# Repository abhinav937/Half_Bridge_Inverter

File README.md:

# for commits on or before Mar 10 2023, the main folder should be renamed as RnD_6th_sem when opened with KiCad. <br/>
## Make sure the folder name is same as the kicad project file name.

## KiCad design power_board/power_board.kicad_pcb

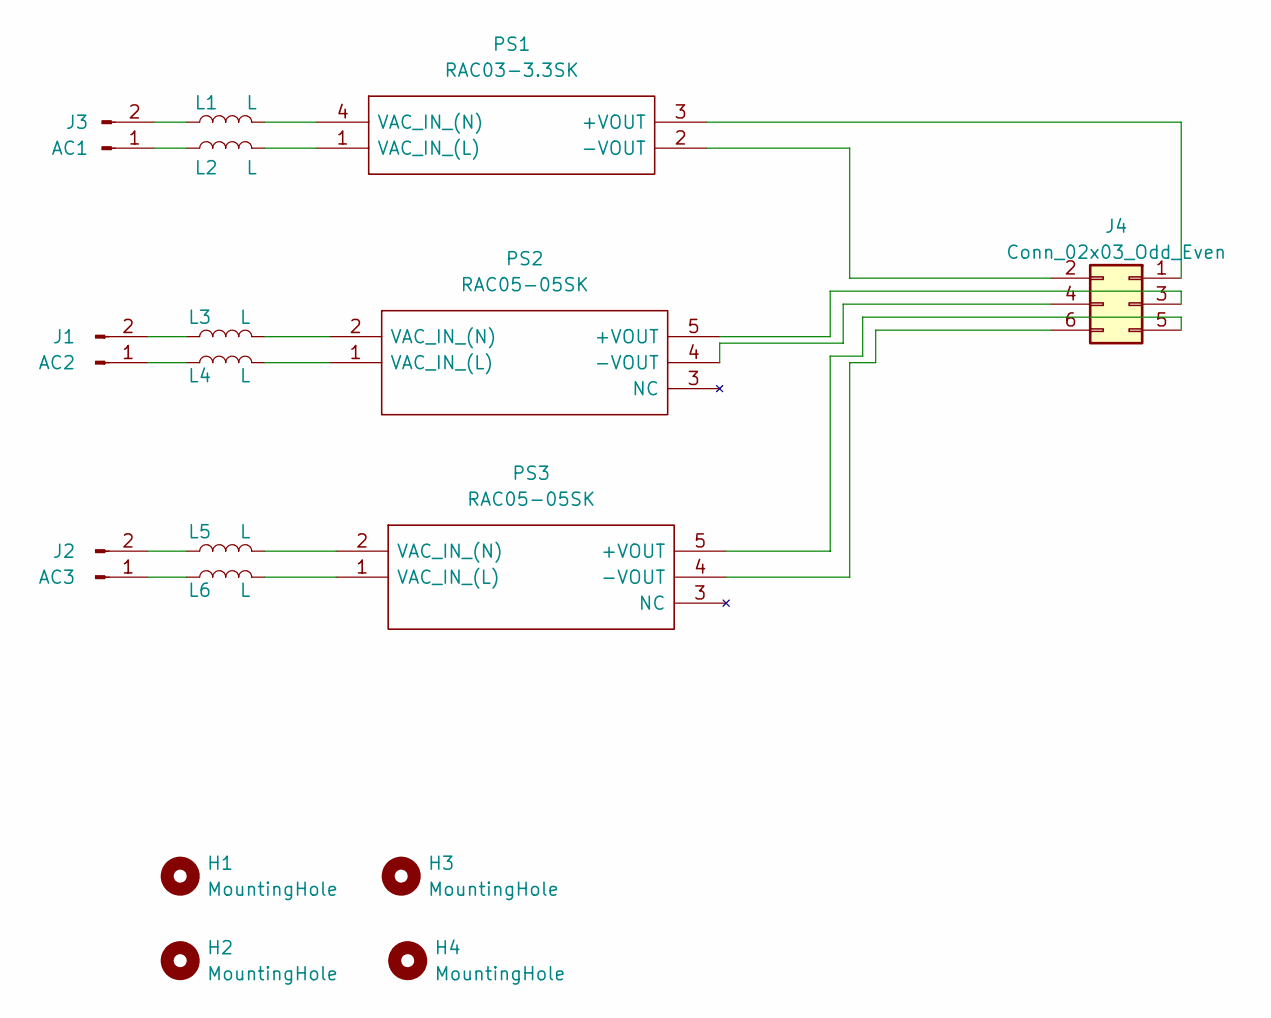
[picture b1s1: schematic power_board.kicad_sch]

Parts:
H1, H2, H3, H4: MountingHole; MountingHole_3.2mm_M3
J1: AC2; Molex_KK-396_A-41791-0002_1x02_P3.96mm_Vertical
J2: AC3; Molex_KK-396_A-41791-0002_1x02_P3.96mm_Vertical
J3: AC1; Molex_KK-396_A-41791-0002_1x02_P3.96mm_Vertical
J4: Conn_02x03_Odd_Even; PinHeader_2x03_P2.54mm_Horizontal
L1, L2, L3, L4, L5, L6: L; C_Rect_L7.0mm_W3.5mm_P5.00mm
PS1: RAC03-3.3SK; RAC0305SK; Mouser Part Number 919-RAC03-3.3SK
PS2, PS3: RAC05-05SK; RAC0505SK; Mouser Part Number 919-RAC05-05SK

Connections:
unnamed: J1.1, L4.1
unnamed: J1.2, L3.1
unnamed: J2.1, L6.1
unnamed: J2.2, L5.1
unnamed: J3.1, L2.1
unnamed: J3.2, L1.1
unnamed: J4.1, PS1.3 (+VOUT)
unnamed: J4.2, PS1.2 (-VOUT)
unnamed: J4.3, PS2.5 (+VOUT)
unnamed: J4.4, PS2.4 (-VOUT)
unnamed: J4.5, PS3.5 (+VOUT)
unnamed: J4.6, PS3.4 (-VOUT)
unnamed: L2.2, PS1.1 (VAC_IN_(L))
unnamed: L1.2, PS1.4 (VAC_IN_(N))
unnamed: L4.2, PS2.1 (VAC_IN_(L))
unnamed: L3.2, PS2.2 (VAC_IN_(N))
unnamed: L6.2, PS3.1 (VAC_IN_(L))
unnamed: L5.2, PS3.2 (VAC_IN_(N))

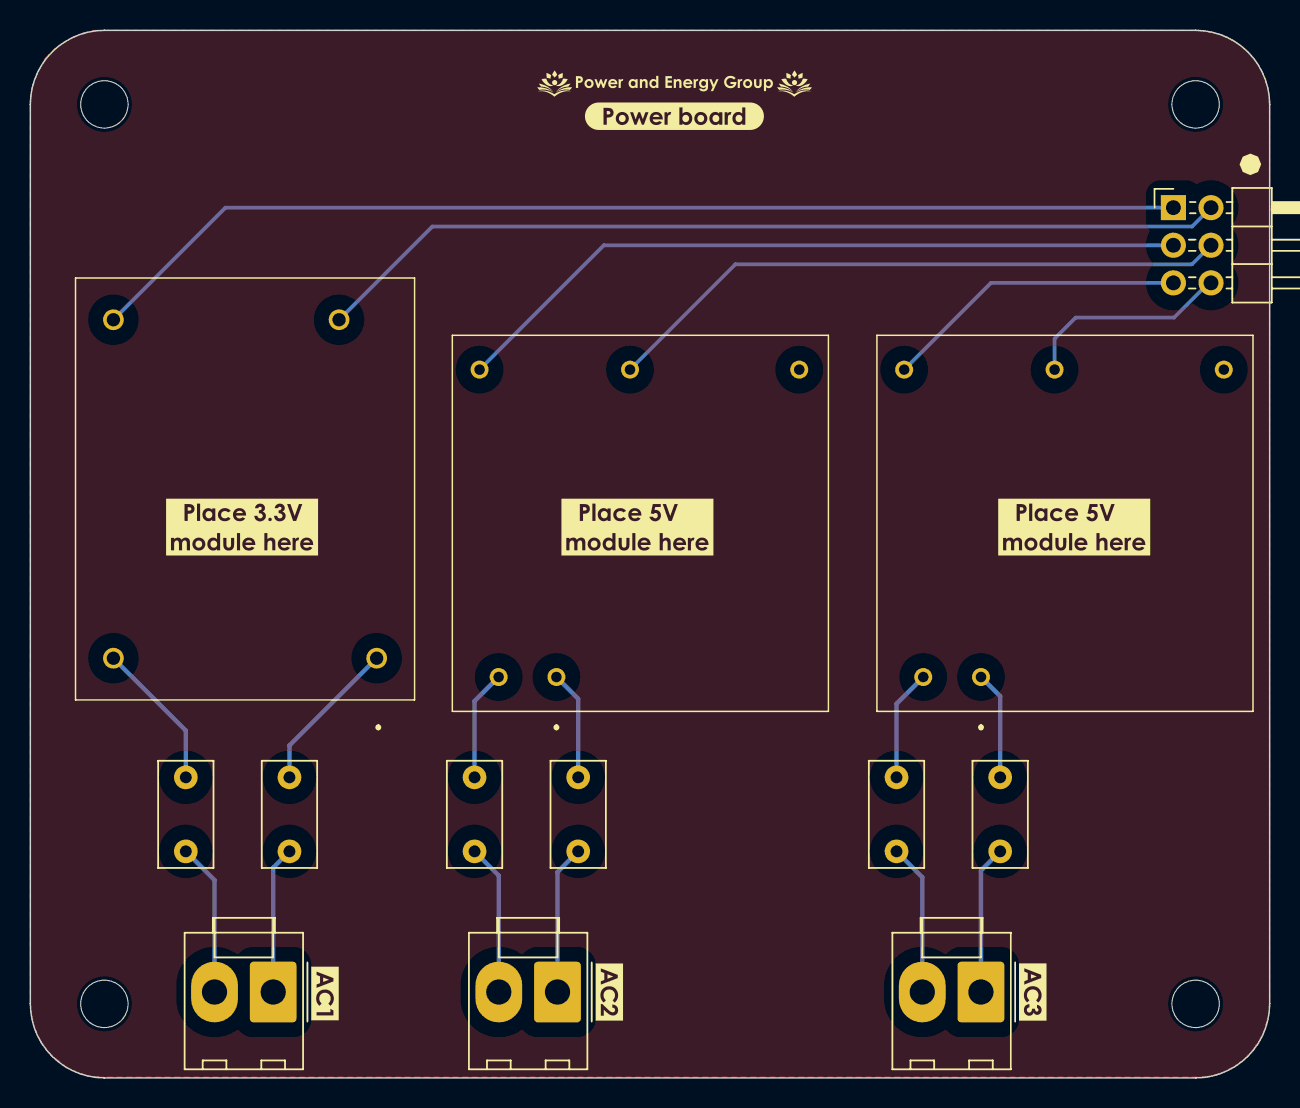
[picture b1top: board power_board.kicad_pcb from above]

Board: 2 copper layers, 83.7 x 70.8 mm, 26 parts (0 on the bottom side), 18 nets.

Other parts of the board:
kibuzzard-63EE9CC7: G***; kibuzzard-63EE9CC7
kibuzzard-63EE9CEB: G***; kibuzzard-63EE9CEB
kibuzzard-63EE9CF3: G***; kibuzzard-63EE9CF3
kibuzzard-63EE9D9B: G***; kibuzzard-63EE9D9B
kibuzzard-63EEA033: G***; kibuzzard-63EEA033
kibuzzard-63EEA069: G***; kibuzzard-63EEA069
kibuzzard-63EEA072: G***; kibuzzard-63EEA072
kibuzzard-640AA3C8: G***; kibuzzard-640AA3C8
kibuzzard-640AA5A5: G***; kibuzzard-640AA5A5

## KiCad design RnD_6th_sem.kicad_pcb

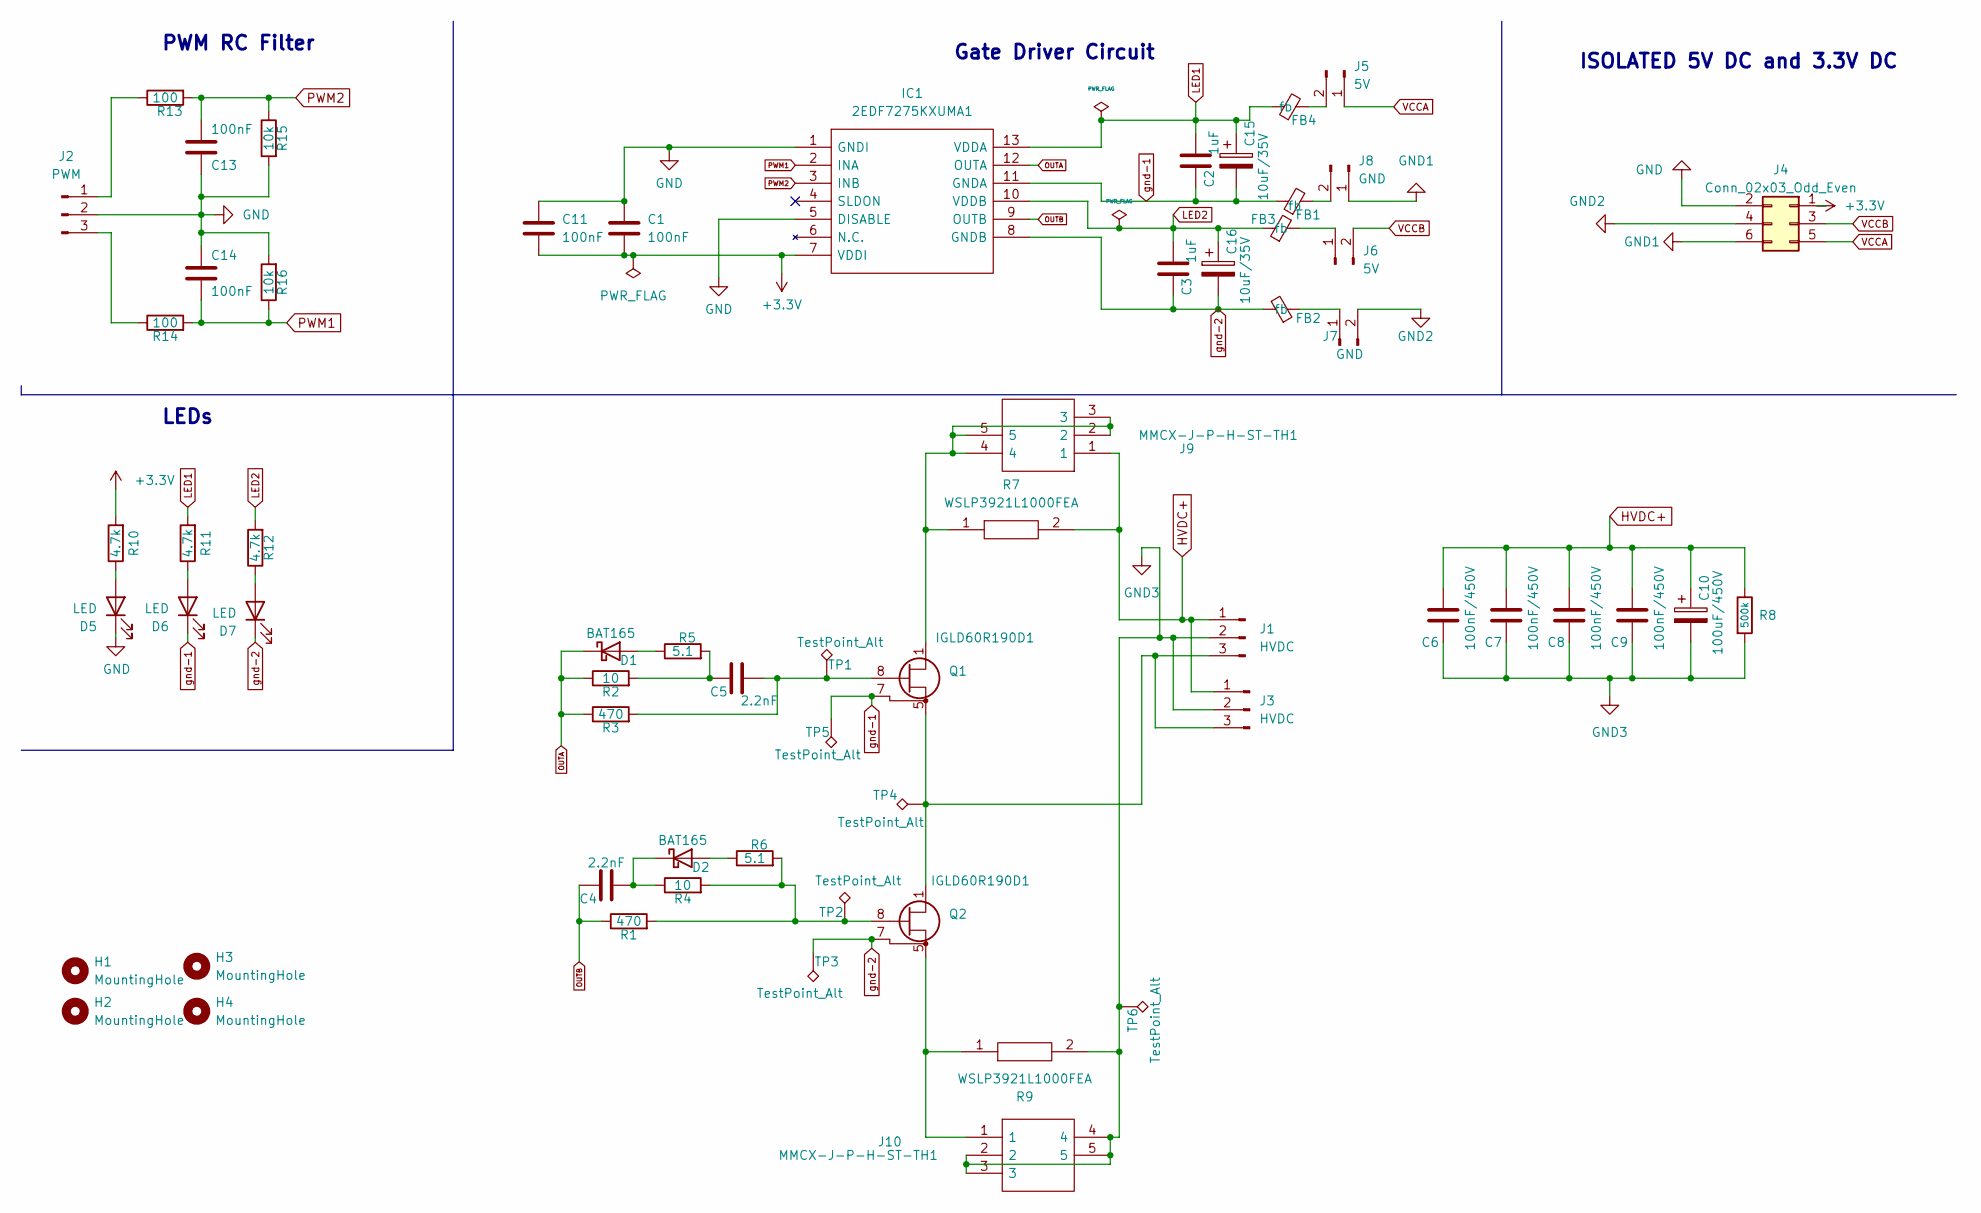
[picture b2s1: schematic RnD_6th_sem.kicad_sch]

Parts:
C1, C11, C13, C14: 100nF; C_0805_2012Metric
C2, C3: 1uF; C_0805_2012Metric
C4, C5: 2.2nF; C_0805_2012Metric
C6, C7, C8, C9: 100nF/450V; C_1206_3216Metric
C10: 100uF/450V; CAPPRD750W80D1825H3200
C15, C16: 10uF/35V; CP_Elec_5x5.3
D1, D2: BAT165; D_SOD-323
D5, D6, D7: LED; LED_0805_2012Metric
FB1, FB2, FB3, FB4: fb; R_0805_2012Metric
H1, H2, H3, H4: MountingHole; MountingHole_3.2mm_M3
IC1: 2EDF7275KXUMA1; TFLGA65P500X500X106-14_13N-V; Mouser Part Number 726-2EDF7275KXUMA1
J1, J3: HVDC; Molex_KK-396_A-41791-0003_1x03_P3.96mm_Vertical
J2: PWM; Molex_KK-254_AE-6410-03A_1x03_P2.54mm_Vertical
J4: Conn_02x03_Odd_Even; PinSocket_2x03_P2.54mm_Horizontal
J5, J6: 5V; PinHeader_1x02_P2.54mm_Vertical
J7, J8: GND; PinHeader_1x02_P2.54mm_Vertical
J9, J10: MMCX-J-P-H-ST-TH1; MMCXJPHSTTH1; Mouser Part Number 200-MMCXJPHSTTH1
Q1, Q2: IGLD60R190D1; Infineon_PG-LSON-8-1
R1, R3: 470; R_0805_2012Metric
R2, R4: 10; R_0805_2012Metric
R5, R6: 5.1; R_0805_2012Metric
R7, R9: WSLP3921L1000FEA; RESC10052X50N; Manufacturer_Part_Number WSLP3921L1000FEA; Mouser Part Number 71-WSLP3921L1000FEA
R8: 500k; R_0805_2012Metric
R10, R11, R12: 4.7k; R_0805_2012Metric
R13, R14: 100; R_0805_2012Metric
R15, R16: 10k; R_0805_2012Metric
TP1, TP2, TP3, TP4, TP5, TP6: TestPoint_Alt; TestPoint_Keystone_5000-5004_Miniature

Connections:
+3.3V: C1.2, C11.2, IC1.7 (VDDI), J4.1, R10.2
GND: C1.1, C11.1, C13.1, C14.1, D5.1 (K), IC1.1 (GNDI), IC1.5 (DISABLE), J2.2, J4.2, R15.2, R16.2
GND1: J4.6, J8.1
GND2: J4.4, J7.2
GND3: C6.2, C7.2, C8.2, C9.2, C10.2, J1.2, J3.2, J10.2, J10.3, J10.4, J10.5, R8.2, R9.2, TP6.1
HVDC+: C6.1, C7.1, C8.1, C9.1, C10.1, J1.1, J3.1, J9.1, R7.2, R8.1
LED1: C2.2, C15.1, FB4.1, IC1.13 (VDDA), R11.2
LED2: C3.2, C16.1, FB3.1, IC1.10 (VDDB), R12.2
unnamed: C5.1, R2.2, R5.2
unnamed: D1.2 (A), R5.1
unnamed: D2.2 (A), R6.1
unnamed: C4.2, D2.1 (K), R4.1
unnamed: D5.2 (A), R10.1
unnamed: D6.2 (A), R11.1
unnamed: D7.2 (A), R12.1
unnamed: J1.3, J3.3, Q1.5 (S), Q1.6 (S), Q1.9 (S), Q2.1 (D), Q2.2 (D), Q2.3 (D), Q2.4 (D), TP4.1
unnamed: J2.1, R13.1
unnamed: J2.3, R14.1
unnamed: FB4.2, J5.2
unnamed: FB3.2, J6.1
unnamed: FB2.1, J7.1
unnamed: FB1.2, J8.2
unnamed: J9.2, J9.3, J9.4, J9.5, Q1.1 (D), Q1.2 (D), Q1.3 (D), Q1.4 (D), R7.1
unnamed: J10.1, Q2.5 (S), Q2.6 (S), Q2.9 (S), R9.1
unnamed: C5.2, Q1.8 (G), R3.2, TP1.1
unnamed: Q2.8 (G), R1.2, R4.2, R6.2, TP2.1
OUTA: D1.1 (K), IC1.12 (OUTA), R2.1, R3.1
OUTB: C4.1, IC1.9 (OUTB), R1.1
PWM1: C14.2, IC1.2 (INA), R14.2, R16.1
PWM2: C13.2, IC1.3 (INB), R13.2, R15.1
VCCA: J4.5, J5.1
VCCB: J4.3, J6.2
gnd-1: C2.1, C15.2, D6.1 (K), FB1.1, IC1.11 (GNDA), Q1.7 (SS), TP5.1
gnd-2: C3.1, C16.2, D7.1 (K), FB2.2, IC1.8 (GNDB), Q2.7 (SS), TP3.1

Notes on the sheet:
LEDs
ISOLATED 5V DC and 3.3V DC
PWM RC Filter
Gate Driver Circuit

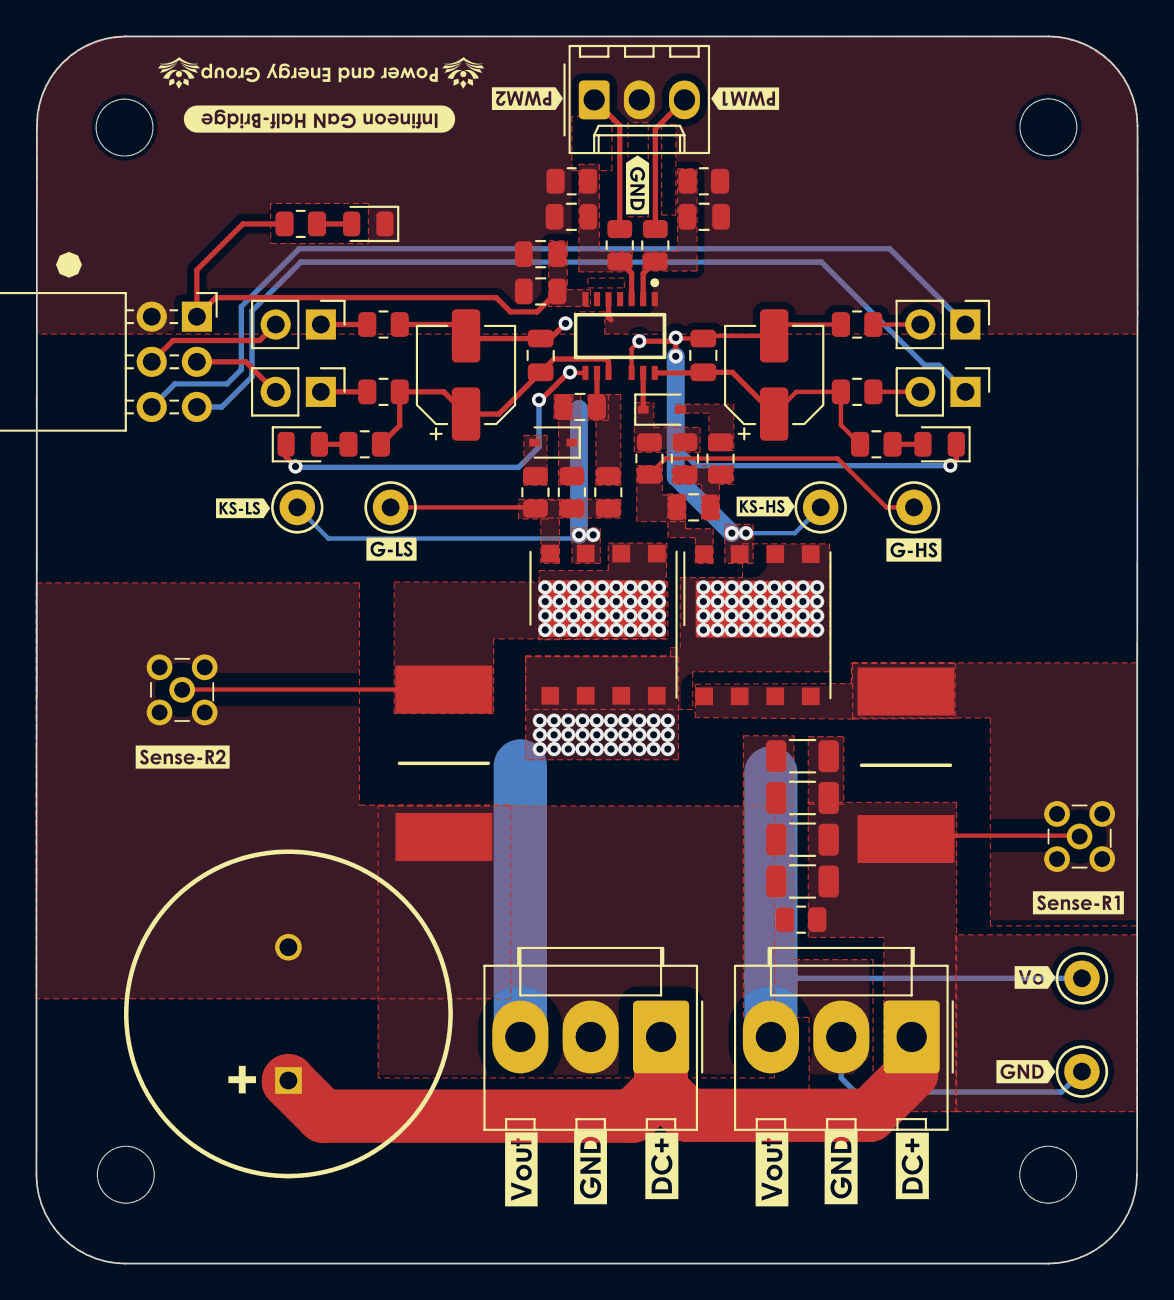
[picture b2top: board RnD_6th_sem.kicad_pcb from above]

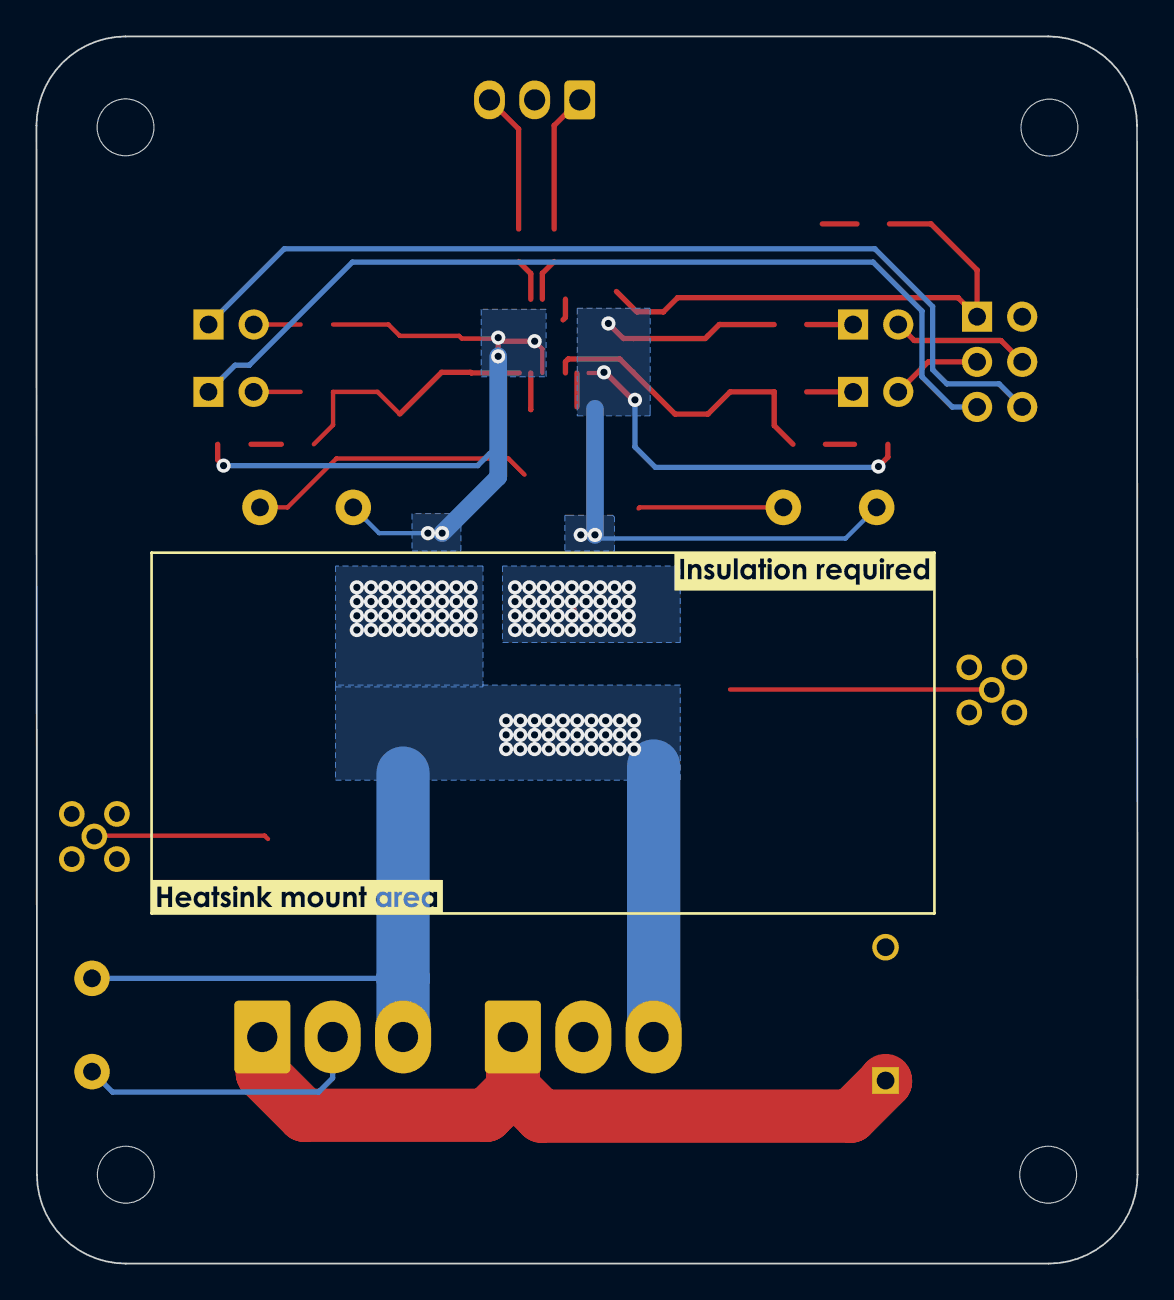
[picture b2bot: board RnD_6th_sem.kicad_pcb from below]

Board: 2 copper layers, 62.0 x 69.1 mm, 86 parts (2 on the bottom side), 34 nets.

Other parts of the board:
kibuzzard-63EDD5C6: G***; kibuzzard-63EDD5C6
kibuzzard-63EDD5E0: G***; kibuzzard-63EDD5E0
kibuzzard-63EDD791: G***; kibuzzard-63EDD791
kibuzzard-63EDDA14: G***; kibuzzard-63EDDA14
kibuzzard-63EE9044, kibuzzard-63EE9044#2: G***; kibuzzard-63EE9044
kibuzzard-63EE9091, kibuzzard-63EE9091#2: G***; kibuzzard-63EE9091
kibuzzard-63FF1A06: G***; kibuzzard-63FF1A06
kibuzzard-63FF1A39: G***; kibuzzard-63FF1A39
kibuzzard-63FF2B27: G***; kibuzzard-63FF2B27
kibuzzard-63FF19DB: G***; kibuzzard-63FF19DB
kibuzzard-63FF19FC: G***; kibuzzard-63FF19FC
kibuzzard-63FF27E9: G***; kibuzzard-63FF27E9
kibuzzard-63FF2952: G***; kibuzzard-63FF2952
kibuzzard-640A1BB7: G***; kibuzzard-640A1BB7
kibuzzard-640A1BC5: G***; kibuzzard-640A1BC5
kibuzzard-640A14F1: G***; kibuzzard-640A14F1
kibuzzard-640A15A1: G***; kibuzzard-640A15A1
kibuzzard-640A15B0: G***; kibuzzard-640A15B0
kibuzzard-640A15B9: G***; kibuzzard-640A15B9
kibuzzard-640AA4D3: G***; kibuzzard-640AA4D3
kibuzzard-640AA404: G***; kibuzzard-640AA404

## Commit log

2023-01-13 updated schema
2023-01-16 added few components
    ferrite beads, leds, rc filter pwm
2023-01-17 PCB layout work started
2023-01-17 added current sense resistors
2023-01-18 updated the schematic
2023-01-21 after ubuntu push
2023-01-31 changed GD Symbol
2023-02-04 updated the schematic
    removed the mmcx connector resistors
2023-02-06 trace routing partially completed
2023-02-13 changed layout
2023-02-13 changes done in schematic
2023-02-15 added power board files
2023-02-16 redesigned the power loop
2023-02-24 updated schematic
2023-02-28 Updated final design
2023-03-01 updated design
    optimized the size and layout
2023-03-01 updated silkscreen
2023-03-01 updated the layout of FB and caps
2023-03-06 Final design
2023-03-08 final design mar-08
2023-03-08 added BOM
2023-03-09 updated the SLDO conn.
2023-03-09 changed TPs location
2023-03-10 added logo
2023-04-15 changed cap values
    PWM RC filter caps changed from 100nF to 0.1nF because of limitations
2023-04-15 renamed the files
